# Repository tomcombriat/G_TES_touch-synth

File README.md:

# G_TES_touch-synth

## Description

## Hardware

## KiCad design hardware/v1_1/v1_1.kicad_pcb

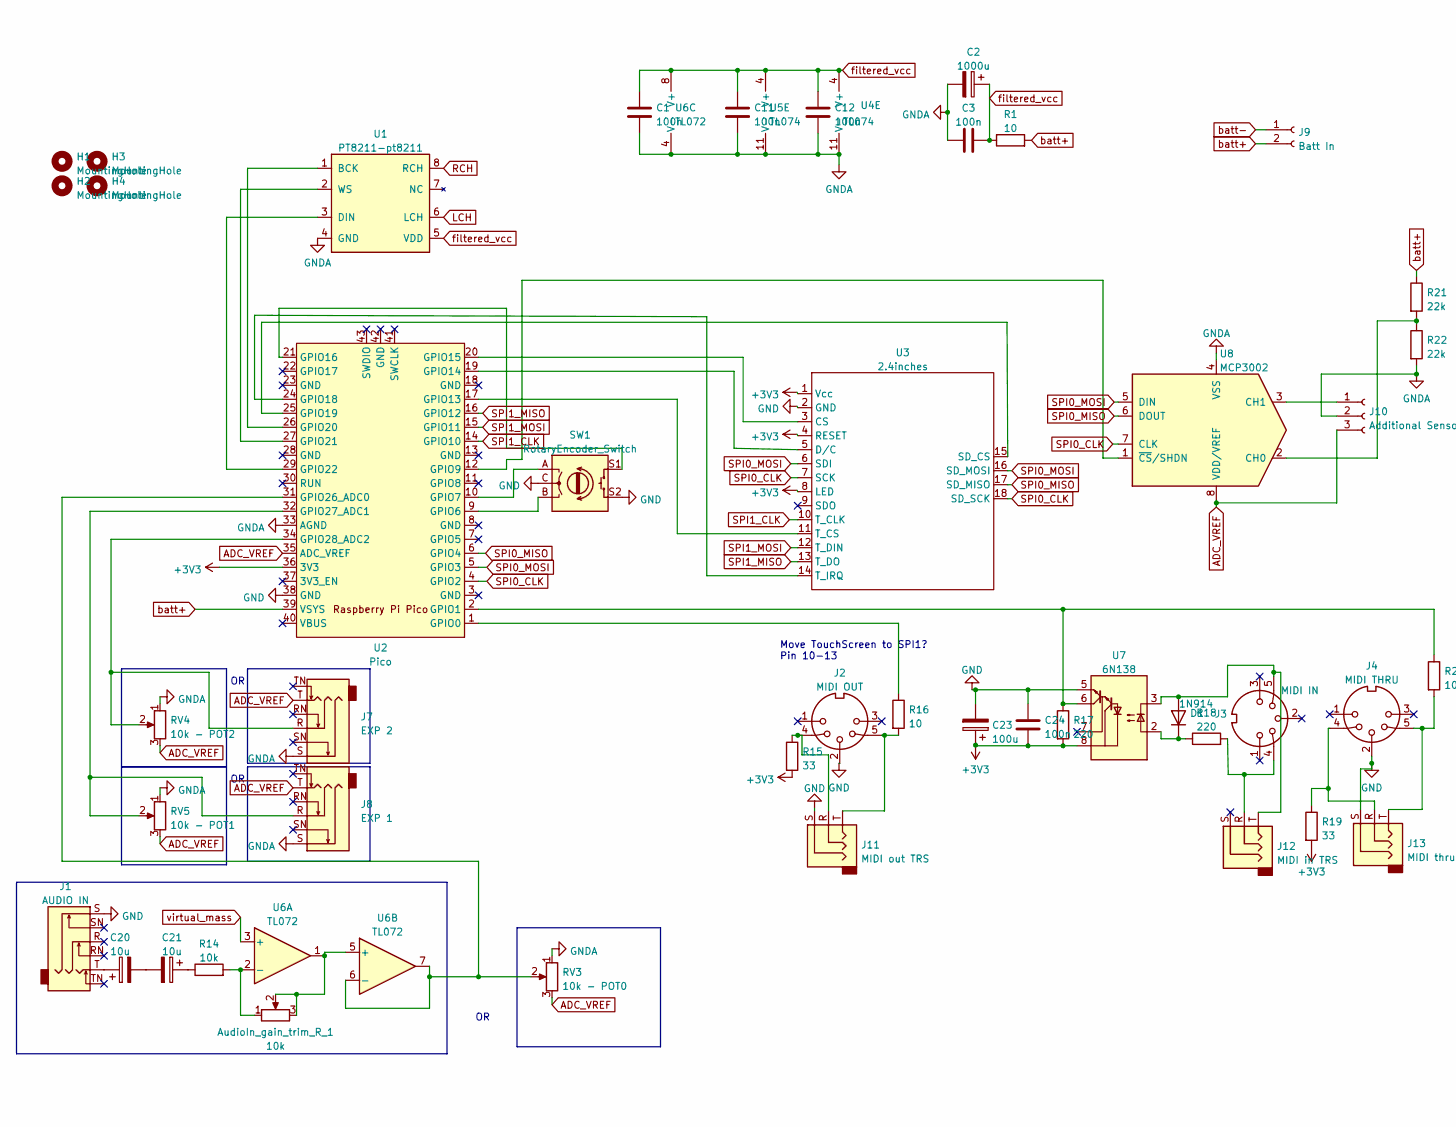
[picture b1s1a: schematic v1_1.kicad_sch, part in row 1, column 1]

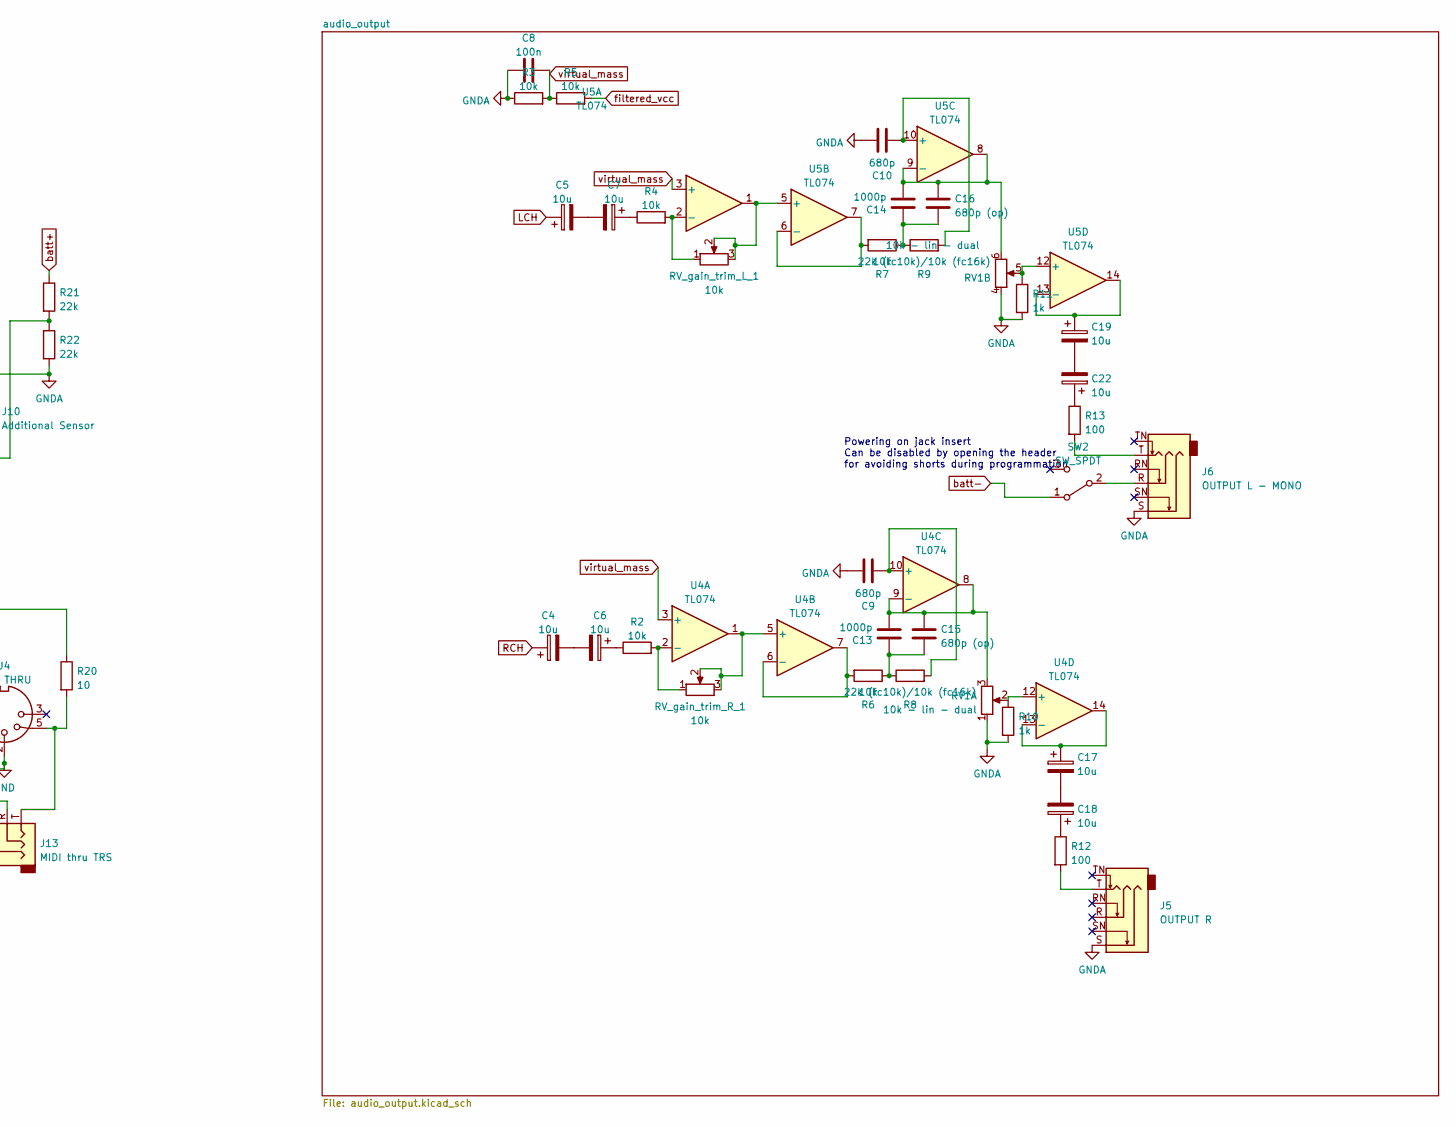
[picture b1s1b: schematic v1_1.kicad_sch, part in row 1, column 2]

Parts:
AudioIn_gain_trim_R_1: 10k; Potentiometer_Runtron_RM-065_Vertical
C1, C3, C11, C12, C24: 100n; C_Axial_L3.8mm_D2.6mm_P7.50mm_Horizontal
C2: 1000u; CP_Radial_D10.0mm_P3.80mm
C4, C5, C6, C7, C17, C18, C19, C20, C21, C22: 10u; CP_Radial_D5.0mm_P2.50mm
C8: 100n; C_Disc_D4.7mm_W2.5mm_P5.00mm
C9, C10: 680p; C_Disc_D5.0mm_W2.5mm_P2.50mm
C13, C14: 1000p; C_Disc_D5.0mm_W2.5mm_P2.50mm
C15, C16: 680p (op); C_Disc_D3.8mm_W2.6mm_P2.50mm
C23: 100u; CP_Radial_D7.5mm_P2.50mm
D1: 1N914; D_DO-34_SOD68_P7.62mm_Horizontal
H1, H2, H3, H4: MountingHole; MountingHole_3.2mm_M3_ISO14580
J1: AUDIO IN; Jack_6.35mm_Neutrik_NMJ6HFD2_Horizontal
J2: MIDI OUT; DS-5 MIDI
J3: MIDI IN; DS-5 MIDI
J4: MIDI THRU; DS-5 MIDI
J5: OUTPUT R; Jack_6.35mm_Neutrik_NMJ6HFD2_Horizontal
J6: OUTPUT L - MONO; Jack_6.35mm_Neutrik_NMJ6HFD2_Horizontal
J7: EXP 2; Jack_6.35mm_Neutrik_NMJ6HFD2_Horizontal
J8: EXP 1; Jack_6.35mm_Neutrik_NMJ6HFD2_Horizontal
J9: Batt In; JST_XH_B2B-XH-A_1x02_P2.50mm_Vertical
J10: Additional Sensor; JST_PH_B3B-PH-K_1x03_P2.00mm_Vertical
J11: MIDI out TRS; PJ-320B
J12: MIDI in TRS; PJ-320B
J13: MIDI thru TRS; PJ-320B
R1, R16, R20: 10; R_Axial_DIN0207_L6.3mm_D2.5mm_P7.62mm_Horizontal
R2, R3, R4, R5, R6, R7, R14: 10k; R_Axial_DIN0207_L6.3mm_D2.5mm_P7.62mm_Horizontal
R8, R9: 22k (fc10k)/10k (fc16k); R_Axial_DIN0207_L6.3mm_D2.5mm_P7.62mm_Horizontal
R10, R11: 1k; R_Axial_DIN0207_L6.3mm_D2.5mm_P7.62mm_Horizontal
R12, R13: 100; R_Axial_DIN0207_L6.3mm_D2.5mm_P7.62mm_Horizontal
R15, R19: 33; R_Axial_DIN0207_L6.3mm_D2.5mm_P7.62mm_Horizontal
R17, R18: 220; R_Axial_DIN0207_L6.3mm_D2.5mm_P7.62mm_Horizontal
R21, R22: 22k; R_Axial_DIN0207_L6.3mm_D2.5mm_P7.62mm_Horizontal
RV1: 10k - lin - dual; Dual Pot RK1114GH
RV3: 10k - POT0; Potentiometer_Alps_RK09K_Single_Vertical
RV4: 10k - POT2; Potentiometer_Alps_RK09K_Single_Vertical
RV5: 10k - POT1; Potentiometer_Alps_RK09K_Single_Vertical
RV_gain_trim_L_1: 10k; Potentiometer_Runtron_RM-065_Vertical
RV_gain_trim_R_1: 10k; Potentiometer_Runtron_RM-065_Vertical
SW1: RotaryEncoder_Switch; RotaryEncoder_Alps_EC11E-Switch_Vertical_H20mm
SW2: SW_SPDT; TO-126-3_Vertical
U1: PT8211-pt8211; SOP-8_3.9x4.9mm_P1.27mm
U2: Pico; RPi_Pico_SMD_TH
U3: 2.4inches; TFT_2.4
U4, U5: TL074; DIP-14_W7.62mm_Socket
U6: TL072; DIP-8_W7.62mm_Socket
U7: 6N138; DIP-8_W7.62mm_Socket
U8: MCP3002; DIP-8_W7.62mm_Socket

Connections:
+3V3: R15.2, R19.2, U2.36 (3V3), U3.1 (Vcc), U3.4 (RESET), U3.8 (LED)
ADC_VREF: J7.T, J8.T, J10.3, RV3.3, RV4.3, RV5.3, U2.35 (ADC_VREF), U8.8 (VDD/VREF)
GND: C23.2, C24.1, J1.S, J2.2, J4.2, J11.S, J13.S, SW1.C, SW1.S2, U2.38 (GND), U3.2 (GND), U7.5 (GND)
GNDA: C1.2, C2.2, C3.2, C8.1, C9.1, C10.1, C11.2, C12.2, J5.S, J6.S, J7.S, J8.S, J10.2, R3.1, R10.2, R11.2, R22.2, RV1.1, RV1.4, RV3.1, RV4.1, RV5.1, U1.4 (GND), U2.33 (AGND), U4.11 (V-), U5.11 (V-), U6.4 (V-), U8.4 (VSS)
LCH: C5.1, U1.6 (LCH)
unnamed: AudioIn_gain_trim_R_1.1, R14.2, U6.2 (-)
unnamed: AudioIn_gain_trim_R_1.2, AudioIn_gain_trim_R_1.3, U6.1, U6.5 (+)
unnamed: C4.2, C6.2
unnamed: C5.2, C7.2
unnamed: C6.1, R2.1
unnamed: C7.1, R4.1
unnamed: C9.2, R8.2, U4.10 (+)
unnamed: C10.2, R9.2, U5.10 (+)
unnamed: C13.1, C15.2, R6.1, R8.1
unnamed: C13.2, C15.1, RV1.3, U4.8, U4.9 (-)
unnamed: C14.1, C16.2, R7.1, R9.1
unnamed: C14.2, C16.1, RV1.6, U5.8, U5.9 (-)
unnamed: C17.1, U4.13 (-), U4.14
unnamed: C17.2, C18.2
unnamed: C18.1, R12.1
unnamed: C19.1, U5.13 (-), U5.14
unnamed: C19.2, C22.2
unnamed: C20.1, J1.T
unnamed: C20.2, C21.2
unnamed: C21.1, R14.1
unnamed: C22.1, R13.1
unnamed: C23.1, C24.2, R17.2, U7.8 (VCC)
unnamed: D1.1 (K), R18.1, U7.2 (C1)
unnamed: D1.2 (A), J3.5, J12.T, U7.3 (C2)
unnamed: J2.4, J11.R, R15.1
unnamed: J2.5, J11.T, R16.2
unnamed: J3.4, J12.R, R18.2
unnamed: J4.5, J13.T, R20.2
unnamed: J5.T, R12.2
unnamed: J6.R, SW2.2 (B)
unnamed: J6.T, R13.2
unnamed: J7.R, RV4.2, U2.34 (GPIO28_ADC2)
unnamed: J8.R, RV5.2, U2.32 (GPIO27_ADC1)
unnamed: J10.1, U8.3 (CH1)
unnamed: R2.2, RV_gain_trim_R_1.1, U4.2 (-)
unnamed: R4.2, RV_gain_trim_L_1.1, U5.2 (-)
unnamed: R6.2, U4.6 (-), U4.7
unnamed: R7.2, U5.6 (-), U5.7
unnamed: R10.1, RV1.2, U4.12 (+)
unnamed: R11.1, RV1.5, U5.12 (+)
unnamed: R16.1, U2.1 (GPIO0)
unnamed: R17.1, R20.1, U2.2 (GPIO1), U7.6 (VO2)
unnamed: J4.4, J13.R, R19.1
unnamed: R21.2, R22.1, U8.2 (CH0)
unnamed: RV3.2, U2.31 (GPIO26_ADC0), U6.6 (-), U6.7
unnamed: RV_gain_trim_L_1.2, RV_gain_trim_L_1.3, U5.1, U5.5 (+)
unnamed: RV_gain_trim_R_1.2, RV_gain_trim_R_1.3, U4.1, U4.5 (+)
unnamed: SW1.A, U2.10 (GPIO7)
unnamed: SW1.B, U2.9 (GPIO6)
unnamed: SW1.S1, U2.21 (GPIO16)
unnamed: U1.1 (BCK), U2.26 (GPIO20)
unnamed: U1.2 (WS), U2.27 (GPIO21)
unnamed: U1.3 (DIN), U2.29 (GPIO22)
unnamed: U2.12 (GPIO9), U8.1 (~CS/SHDN)
unnamed: U2.17 (GPIO13), U3.11 (T_CS)
unnamed: U2.19 (GPIO14), U3.5 (D/C)
unnamed: U2.20 (GPIO15), U3.3 (CS)
unnamed: U2.24 (GPIO18), U3.14 (T_IRQ)
unnamed: U2.25 (GPIO19), U3.15 (SD_CS)
RCH: C4.1, U1.8 (RCH)
SPI0_CLK: U2.4 (GPIO2), U3.7 (SCK), U3.18 (SD_SCK), U8.7 (CLK)
SPI0_MISO: U2.6 (GPIO4), U3.17 (SD_MISO), U8.6 (DOUT)
SPI0_MOSI: U2.5 (GPIO3), U3.6 (SDI), U3.16 (SD_MOSI), U8.5 (DIN)
SPI1_CLK: U2.14 (GPIO10), U3.10 (T_CLK)
SPI1_MISO: U2.16 (GPIO12), U3.13 (T_DO)
SPI1_MOSI: U2.15 (GPIO11), U3.12 (T_DIN)
batt+: J9.2, R1.2, R21.1, U2.39 (VSYS)
batt-: J9.1, SW2.1 (A)
filtered_vcc: C1.1, C2.1, C3.1, C11.1, C12.1, R1.1, R5.2, U1.5 (VDD), U4.4 (V+), U5.4 (V+), U6.8 (V+)
virtual_mass: C8.2, R3.2, R5.1, U4.3 (+), U5.3 (+), U6.3 (+)

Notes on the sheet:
Powering on jack insert Can be disabled by opening the header for avoiding shorts during programmation
Move TouchScreen to SPI1? Pin 10-13

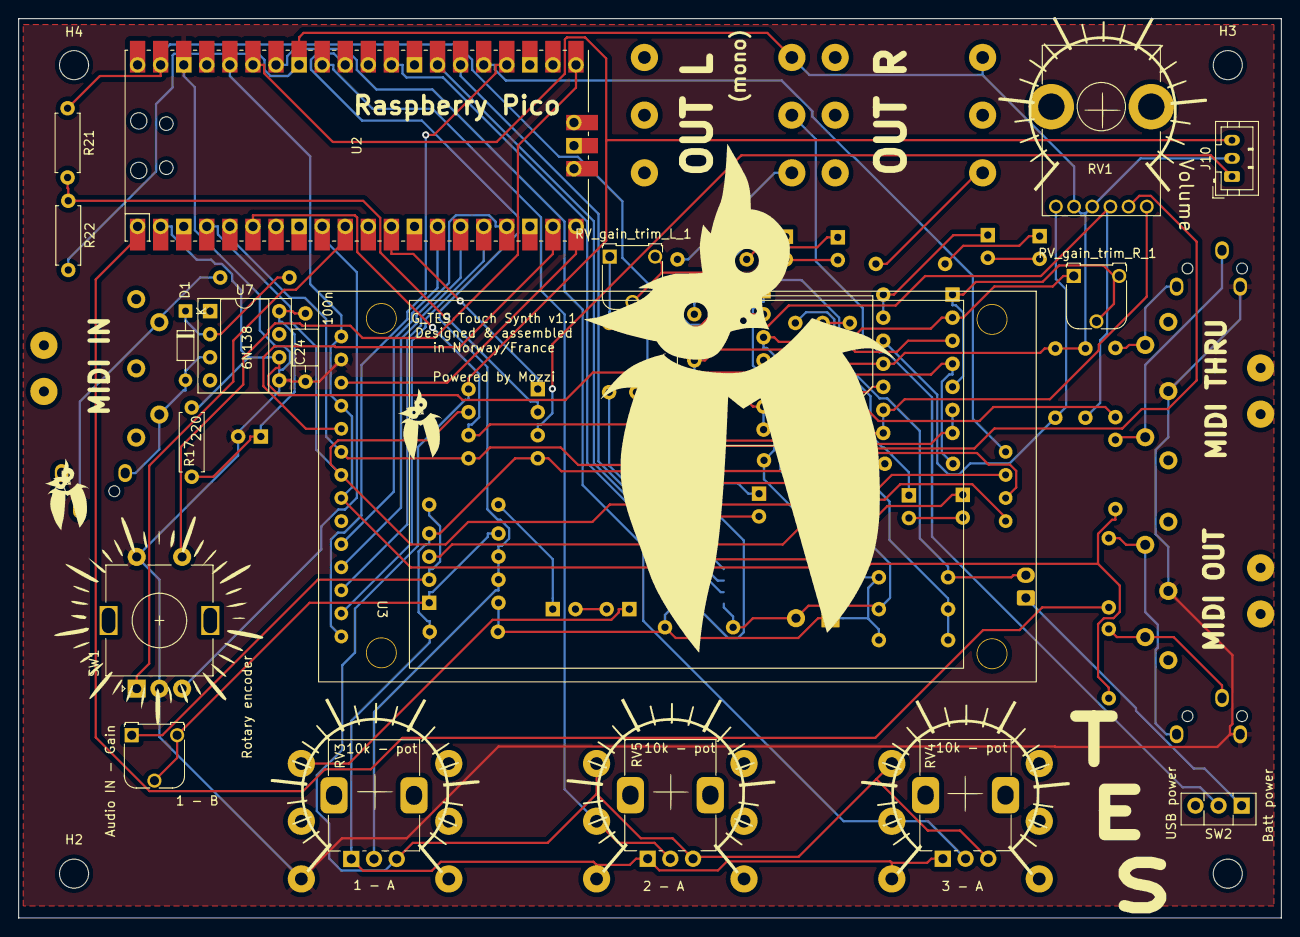
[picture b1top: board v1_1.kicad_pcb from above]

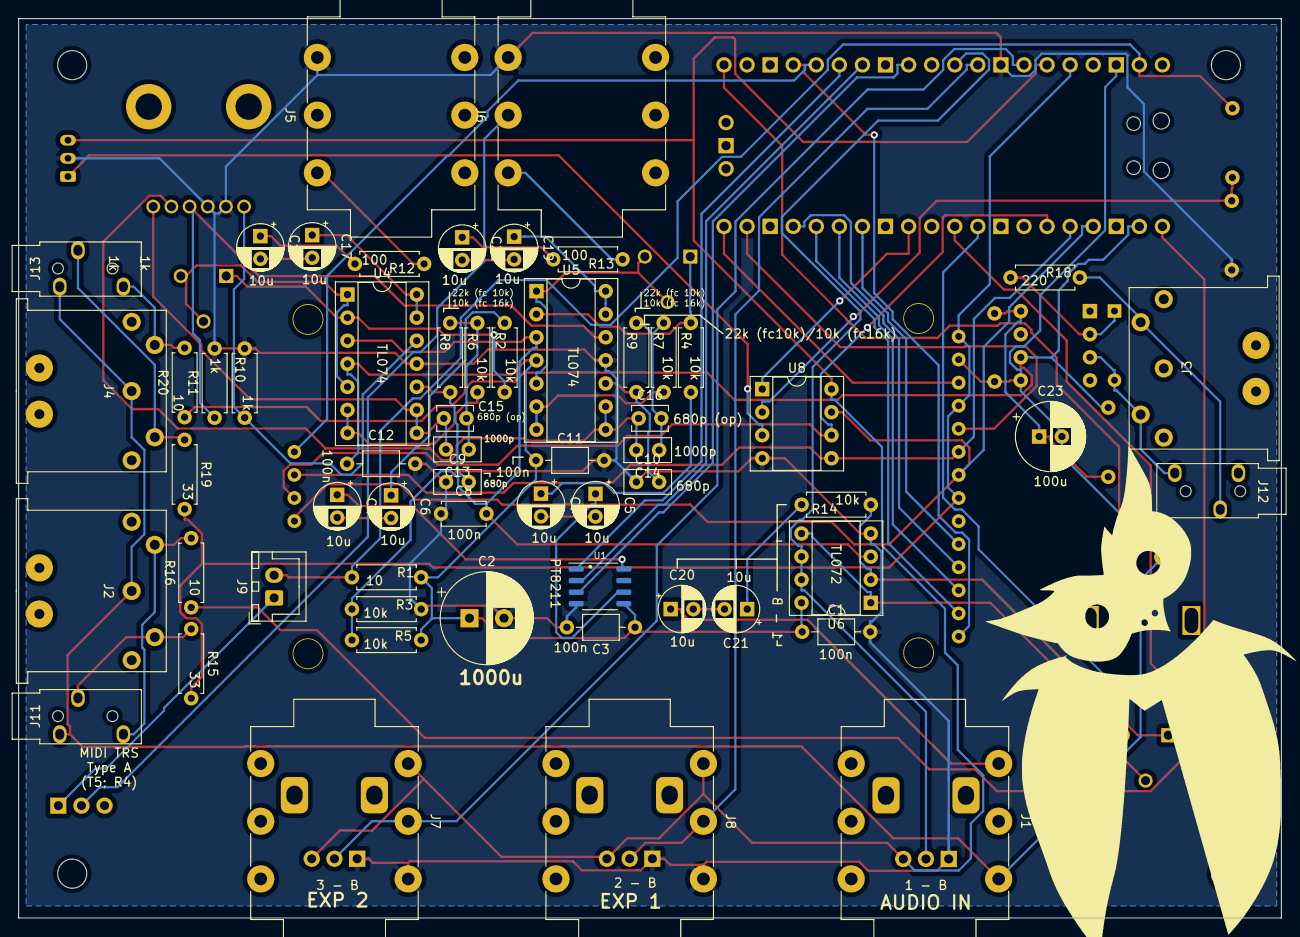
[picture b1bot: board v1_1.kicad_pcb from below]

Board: 2 copper layers, 139.0 x 99.0 mm, 89 parts (60 on the bottom side), 75 nets.

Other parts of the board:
G1, G2, G3: LOGO; pot_dial
G_owl1: LOGO; owl_F_50x70
Gowl2: LOGO; owl_7x10
Gowl_bot: LOGO; owl_F_50x70
Grot_enc: LOGO; rot_dial
Gvol: LOGO; pot_dial

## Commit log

2023-02-09 Added kicad pico footprint and component
2023-02-09 Kicad wired screen and rp
2023-02-09 Added prototype of out filter
2023-02-09 Moved kicad files
2023-02-09 Added kicad_sym for pt8211 and screen
2023-02-11 Second output filter
2023-02-12 Added input audio to schema
2023-02-12 Finished audio output schema, add midi in
2023-02-12 Added expression pedals
2023-02-12 Added rotary, and SD SPI card. Tested rotary
2023-02-13 Added battery connector, started symbol association
2023-02-14 Continued components assig
2023-02-15 Assignation of easy components
2023-02-15 Added DIN5 Midi component
2023-02-15 Corrected DIN5 stamp
2023-02-15 Added stamp dual pot
2023-02-15 Added screen stamp
2023-02-16 Added the owl
2023-02-16 started pcb
2023-02-16 Shifted all connectors to B-side
2023-02-16 Continued PCB placing
2023-02-16 First draft on PCB placing
2023-02-19 Added header for battery or USB powering
2023-02-19 Added mounting holes - Cleaned PCB placement
2023-02-19 PCB routing and mass planes
2023-02-19 Updated mass planes
2023-02-19 Updated pcb
2023-02-19 Moved optocoupler to the digital side, labels placement
2023-02-19 Labelling pcb - placed the owl
2023-02-19 Replace power selection with a switch
2023-02-19 Added dial serigraphy
2023-02-19 Better ground plane?
2023-02-19 Improved silk
2023-02-20 Added gerber files
2023-03-11 Switched pot polarity for v1.1
2023-03-12 Updated test with visual pot
2023-03-25 Updated test sketch
2023-03-27 Updated example for testing
2023-03-27 Updated example
2023-04-12 Updated example with templated parameters
2023-04-24 Corrected output filter
2023-05-01 Update example script
2023-05-01 Corrected power net, 3V3 is not 3.3V
2023-05-08 Updated test script to new things in lib
2023-05-18 Ajout nouveau test : simpleGBF
2023-09-20 Added low battery sensing on digitalPin
2023-09-26 SD card check
2023-09-30 Component assign
2023-09-30 Added silk symbols
2023-10-25 Added ADC component
2023-11-01 Added commnet
2023-11-04 Switch tacticle to SPI1
2023-11-04 Added ADC for battery ctrl
2023-11-04 Better wires, to some extend
2023-11-04 Added connector for additionnal sensor
2023-11-11 Re-routed pcb for 1.1
2023-11-12 Added MIDI over TRS connector
2023-11-13 Routing
2023-11-13 Added Gerber
2024-06-19 Sketch for simplified vrison of GT_lib
2024-06-20 Added and tested modif from the lib
2024-06-24 Added test of several pot with lpf
2024-06-25 Starting interacting with touchscreen
2024-08-01 Udated to new paradigm for inputs (not very different, just to allow changes)
2024-08-01 BugFix
2024-08-04 Example of kind of fully workable basic drone synth
2024-08-06 More modularization, added touch
2024-08-06 Better synthesis
2024-08-10 Added buttons
2024-09-23 Updated sketch to new features of lib
2024-12-05 Removed deprecated sketches
2024-12-26 Added screen calibration
